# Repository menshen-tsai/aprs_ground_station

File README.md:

# APRS Ground Station Hardware and Firmware/Software for Hand-On Class

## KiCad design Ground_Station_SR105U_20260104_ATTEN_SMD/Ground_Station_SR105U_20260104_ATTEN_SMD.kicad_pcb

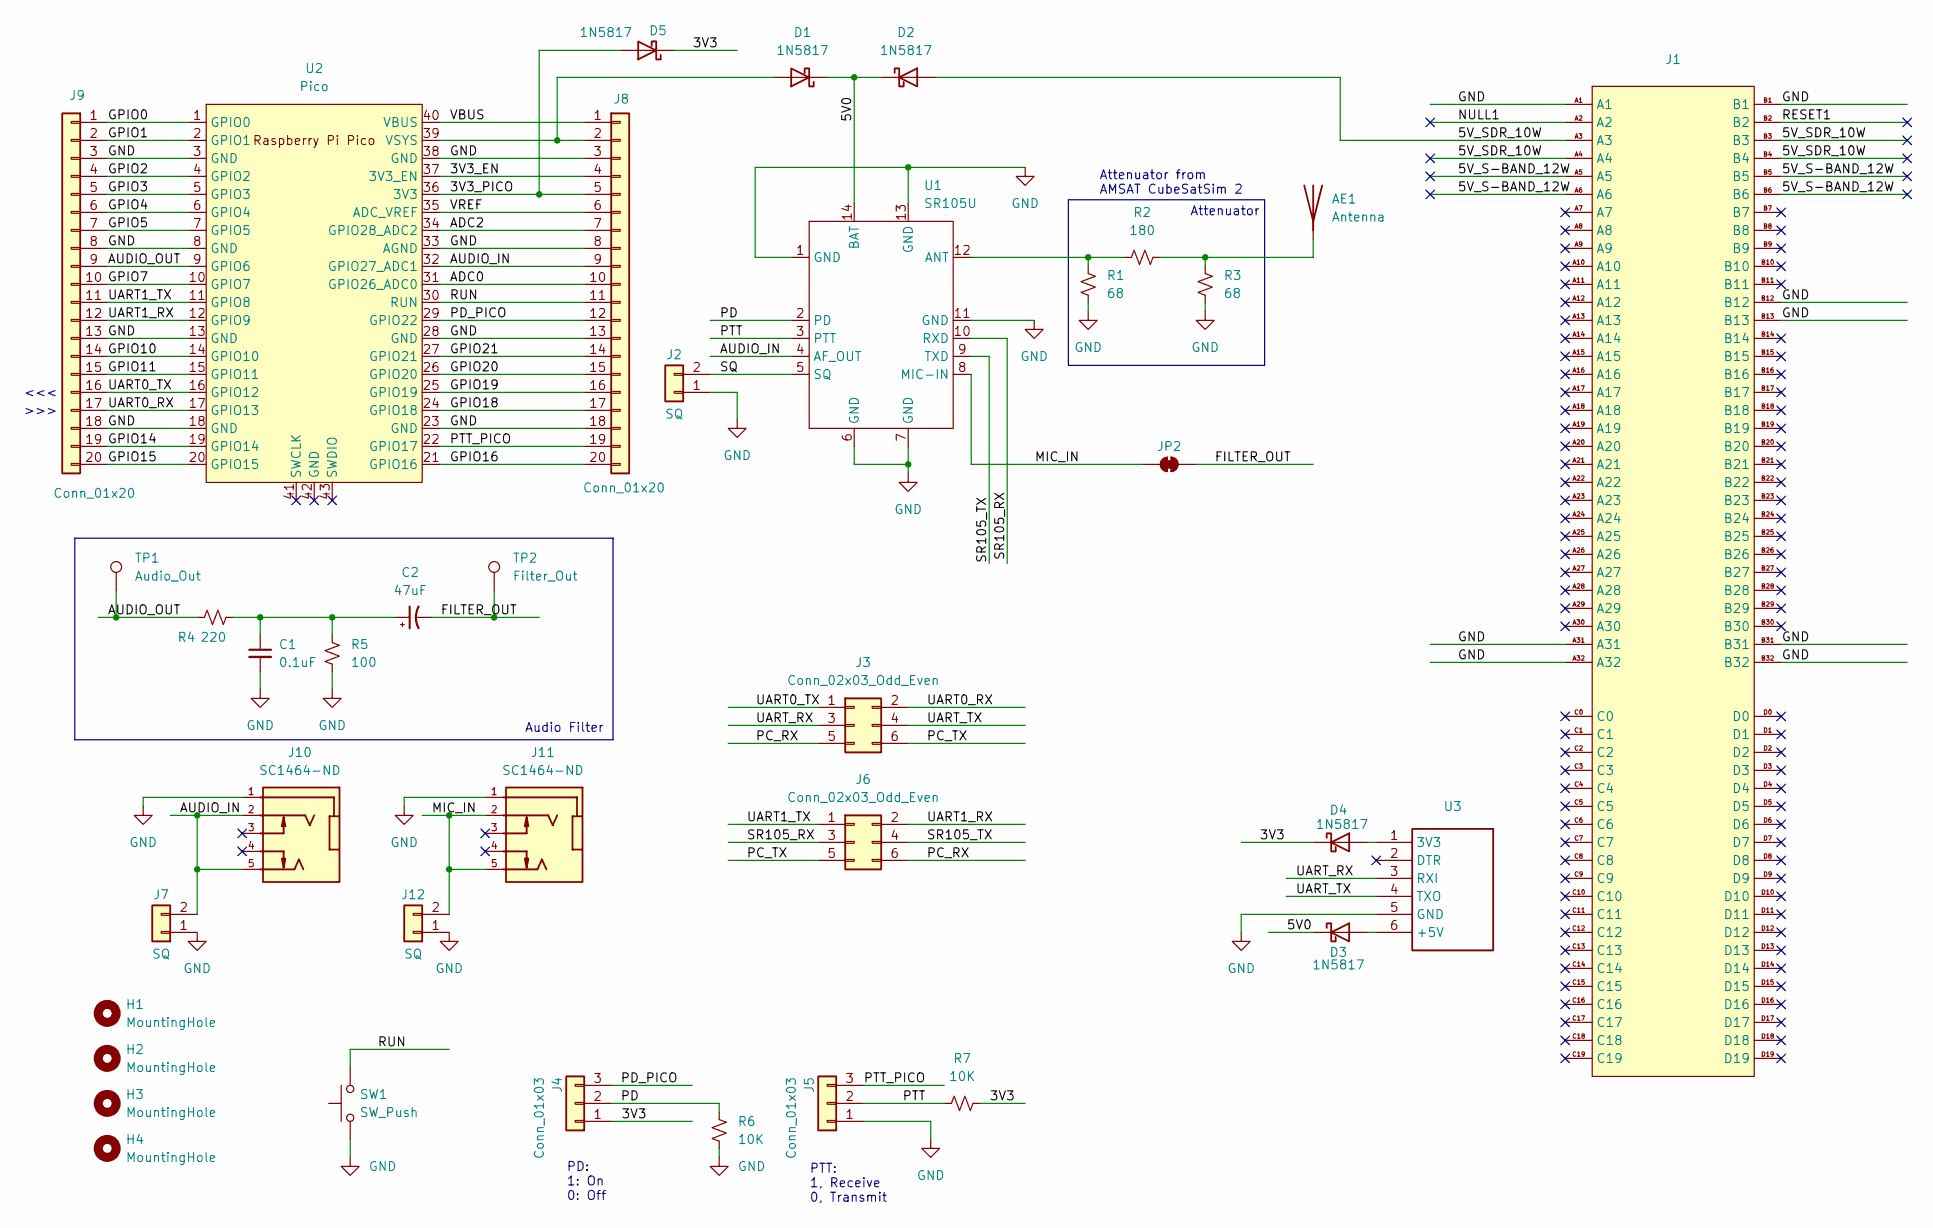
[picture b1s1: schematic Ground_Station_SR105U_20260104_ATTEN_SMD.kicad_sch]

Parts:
AE1: Antenna; SMA_Amphenol_901-144_Vertical
C1: 0.1uF; C_Disc_D4.7mm_W2.5mm_P5.00mm
C2: 47uF; CP_Radial_D5.0mm_P2.00mm
D1, D2, D3: 1N5817; D_DO-41_SOD81_P10.16mm_Horizontal
D4, D5: 1N5817; Diode_TH
H1, H2, H3, H4: MountingHole; MountingHole_3.2mm_M3_Pad_Via
J1: PC104_16bit_Connector
J2, J7, J12: SQ; PinHeader_1x02_P2.54mm_Vertical
J3, J6: Conn_02x03_Odd_Even; PinHeader_2x03_P2.54mm_Vertical
J4, J5: Conn_01x03; PinHeader_1x03_P2.54mm_Vertical
J8, J9: Conn_01x20; PinHeader_1x20_P2.54mm_Vertical
J10, J11: SC1464-ND; Jack_3.5mm_CUI_SJ1-3525N_Horizontal
JP2: SolderJumper_2_Bridged; SolderJumper-2_P1.3mm_Bridged_Pad1.0x1.5mm
R1, R3: 68; R_1206_3216Metric
R2: 180; R_1206_3216Metric
R4: 220; R_Axial_DIN0207_L6.3mm_D2.5mm_P7.62mm_Horizontal
R5: 100; R_Axial_DIN0207_L6.3mm_D2.5mm_P7.62mm_Horizontal
R6, R7: 10K; R_Axial_DIN0207_L6.3mm_D2.5mm_P7.62mm_Horizontal
SW1: SW_Push; SW_PUSH_1P1T_6x3.5mm_H4.3_APEM_MJTP1243
TP1: Audio_Out; TestPoint_THTPad_D1.5mm_Drill0.7mm
TP2: Filter_Out; TestPoint_THTPad_D1.5mm_Drill0.7mm
U1: SR105U
U2: Pico; RPi_Pico_TH
U3: USB_UART_Module_New

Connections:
/3V3: D4.1 (K), D5.1 (K), J4.1, R7.1
/3V3_EN: J8.4, U2.37 (3V3_EN)
/3V3_PICO: D5.2 (A), J8.5, U2.36 (3V3)
/5V0: D1.1 (K), D2.1 (K), D3.1 (K), U1.14 (BAT)
/5V_S-BAND_12W: J1.A5, J1.A6, J1.B5, J1.B6
/5V_SDR_10W: D2.2 (A), J1.A3, J1.A4, J1.B3, J1.B4
/ADC0: J8.10, U2.31 (GPIO26_ADC0)
/ADC2: J8.7, U2.34 (GPIO28_ADC2)
/AUDIO_IN: J7.2, J8.9, J10.2, J10.5, U1.4 (AF_OUT), U2.32 (GPIO27_ADC1)
/AUDIO_OUT: J9.9, R4.1, TP1.1, U2.9 (GPIO6)
/FILTER_OUT: C2.2, JP2.2 (B), TP2.1
/GPIO0: J9.1, U2.1 (GPIO0)
/GPIO1: J9.2, U2.2 (GPIO1)
/GPIO2: J9.4, U2.4 (GPIO2)
/GPIO3: J9.5, U2.5 (GPIO3)
/GPIO4: J9.6, U2.6 (GPIO4)
/GPIO5: J9.7, U2.7 (GPIO5)
/GPIO7: J9.10, U2.10 (GPIO7)
/GPIO10: J9.14, U2.14 (GPIO10)
/GPIO11: J9.15, U2.15 (GPIO11)
/GPIO14: J9.19, U2.19 (GPIO14)
/GPIO15: J9.20, U2.20 (GPIO15)
/GPIO16: J8.20, U2.21 (GPIO16)
/GPIO18: J8.17, U2.24 (GPIO18)
/GPIO19: J8.16, U2.25 (GPIO19)
/GPIO20: J8.15, U2.26 (GPIO20)
/GPIO21: J8.14, U2.27 (GPIO21)
/MIC_IN: J11.2, J11.5, J12.2, JP2.1 (A), U1.8 (MIC-IN)
/NULL1: J1.A2
/PC_RX: J3.5, J6.6
/PC_TX: J3.6, J6.5
/PD: J4.2, R6.2, U1.2 (PD)
/PD_PICO: J4.3, J8.12, U2.29 (GPIO22)
/PTT: J5.2, R7.2, U1.3 (PTT)
/PTT_PICO: J5.3, J8.19, U2.22 (GPIO17)
/RESET1: J1.B2
/RUN: J8.11, SW1.2, U2.30 (RUN)
/SQ: J2.2, U1.5 (SQ)
/SR105_RX: J6.3, U1.10 (RXD)
/SR105_TX: J6.4, U1.9 (TXD)
/UART0_RX: J3.2, J9.17, U2.17 (GPIO13)
/UART0_TX: J3.1, J9.16, U2.16 (GPIO12)
/UART1_RX: J6.2, J9.12, U2.12 (GPIO9)
/UART1_TX: J6.1, J9.11, U2.11 (GPIO8)
/UART_RX: J3.3, U3.3 (RXI)
/UART_TX: J3.4, U3.4 (TXO)
/VBUS: J8.1, U2.40 (VBUS)
/VREF: J8.6, U2.35 (ADC_VREF)
GND: C1.2, J1.A1, J1.A31, J1.A32, J1.B1, J1.B12, J1.B13, J1.B31, J1.B32, J2.1, J5.1, J7.1, J8.3, J8.8, J8.13, J8.18, J9.3, J9.8, J9.13, J9.18, J10.1, J11.1, J12.1, R1.2, R3.2, R5.1, R6.1, SW1.1, U1.1 (GND), U1.6 (GND), U1.7 (GND), U1.11 (GND), U1.13 (GND), U2.3 (GND), U2.8 (GND), U2.13 (GND), U2.18 (GND), U2.23 (GND), U2.28 (GND), U2.33 (AGND), U2.38 (GND), U3.5 (GND)
unnamed: AE1.1 (A), R2.2, R3.1
unnamed: C1.1, C2.1, R4.2, R5.2
unnamed: D1.2 (A), J8.2, U2.39 (VSYS)
unnamed: D3.2 (A), U3.6 (+5V)
unnamed: D4.2 (A), U3.1 (3V3)
unnamed: R1.1, R2.1, U1.12 (ANT)

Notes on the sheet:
PD: 1: On 0: Off
Attenuator
PTT: 1, Receive 0, Transmit
>>>
<<<
Attenuator from AMSAT CubeSatSim 2
Audio Filter

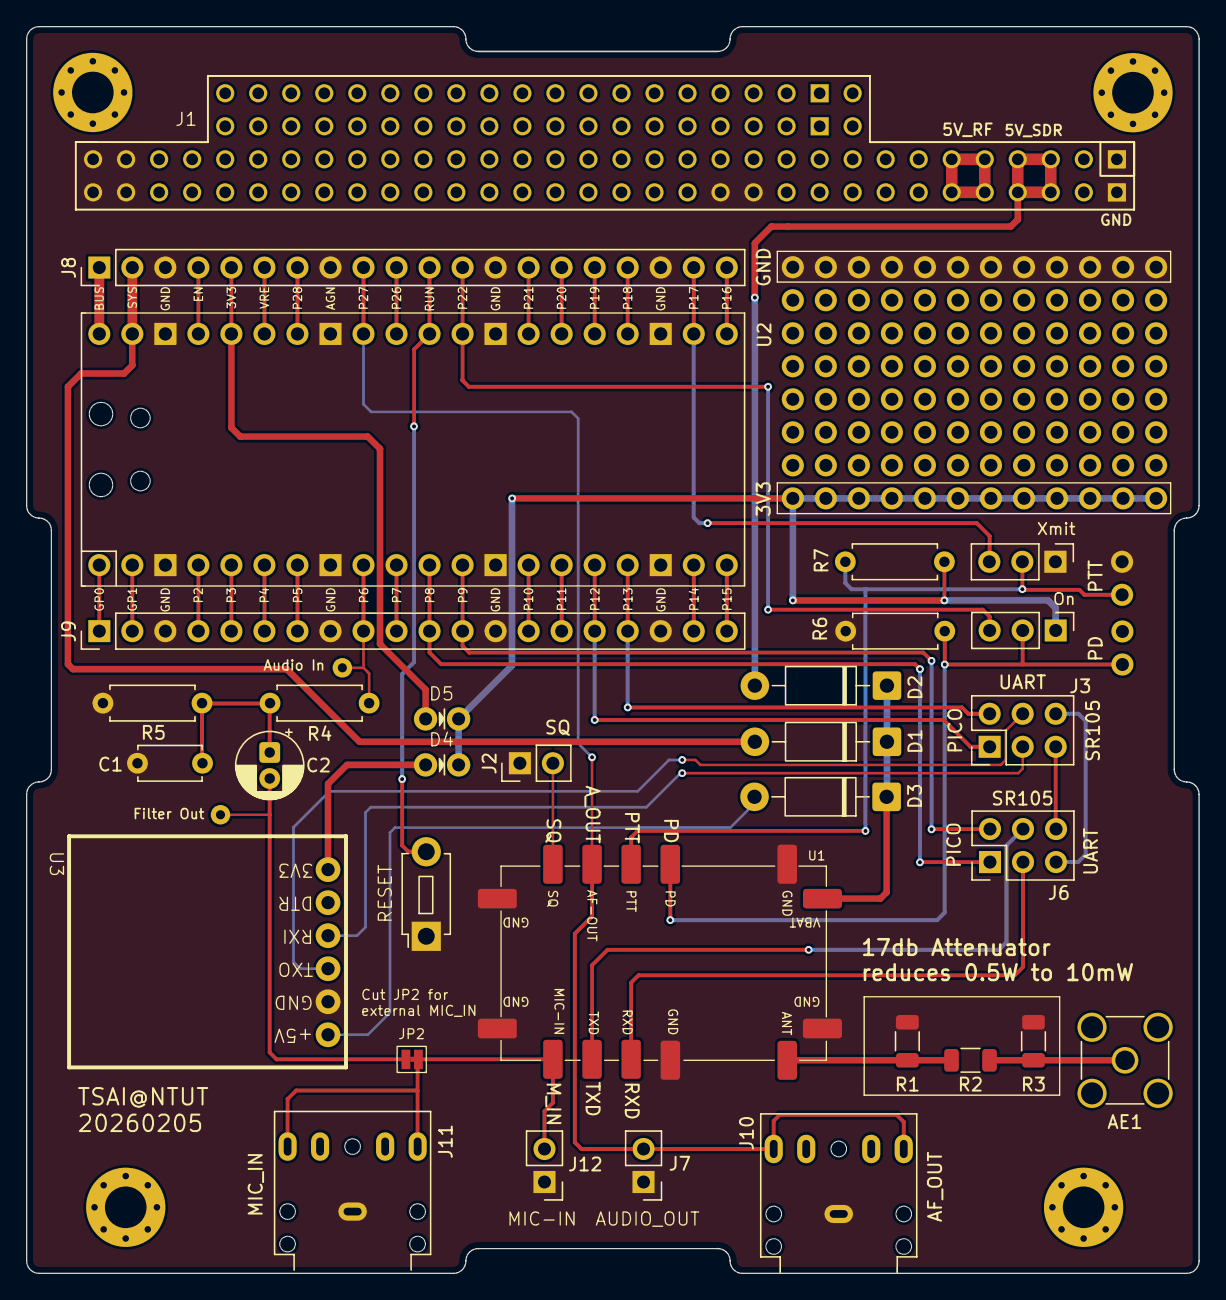
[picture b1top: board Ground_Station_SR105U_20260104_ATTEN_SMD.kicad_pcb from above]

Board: 2 copper layers, 90.1 x 95.9 mm, 38 parts (0 on the bottom side), 53 nets.

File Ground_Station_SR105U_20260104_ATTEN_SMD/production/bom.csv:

Designator,Footprint,Quantity,Value,LCSC Part #
AE1,SMA_Amphenol_901-144_Vertical,1,Antenna,
C1,C_Disc_D4.7mm_W2.5mm_P5.00mm,1,0.1uF,
C2,CP_Radial_D5.0mm_P2.00mm,1,47uF,
"D1, D2, D3",D_DO-41_SOD81_P10.16mm_Horizontal,3,1N5817,
"D4, D5",Diode_TH,2,1N5817,
"H1, H2, H3, H4",MountingHole_3.2mm_M3_Pad_Via,4,MountingHole,
J1,PC104_16bit_Connector,1,~,
"J10, J11",Jack_3.5mm_CUI_SJ1-3525N_Horizontal,2,SC1464-ND,
"J12, J2, J7",PinHeader_1x02_P2.54mm_Vertical,3,SQ,
"J3, J6",PinHeader_2x03_P2.54mm_Vertical,2,Conn_02x03_Odd_Even,
"J4, J5",PinHeader_1x03_P2.54mm_Vertical,2,Conn_01x03,
"J8, J9",PinHeader_1x20_P2.54mm_Vertical,2,Conn_01x20,
"R1, R3",1206,2,68,
R2,1206,1,180,
R4,R_Axial_DIN0207_L6.3mm_D2.5mm_P7.62mm_Horizontal,1,220,
R5,R_Axial_DIN0207_L6.3mm_D2.5mm_P7.62mm_Horizontal,1,100,
"R6, R7",R_Axial_DIN0207_L6.3mm_D2.5mm_P7.62mm_Horizontal,2,10K,
SW1,SW_PUSH_1P1T_6x3.5mm_H4.3_APEM_MJTP1243,1,SW_Push,
TP1,TestPoint_THTPad_D1.5mm_Drill0.7mm,1,Audio_Out,
TP2,TestPoint_THTPad_D1.5mm_Drill0.7mm,1,Filter_Out,
U1,SR105U,1,SR105U,
U2,RPi_Pico_TH,1,Pico,
U3,USB_UART_Module_New,1,~,

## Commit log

2026-01-30 Add Kicad design files.
2026-01-30 Add old Kicad design files. PCB is based on this design.
2026-01-30 Add Arduino codes, python code.
2026-01-30 Update APRS_PICO.ppt, add one page to explain bi-directional configuration of the ground station.
2026-01-30 Add compiled files, bin, elf, uf2.
2026-02-05 Add test points for audio filter
